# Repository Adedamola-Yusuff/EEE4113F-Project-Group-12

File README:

# EEE4113F_Group12_PCB
## Overview
This repository was used for Group 12 (of the 2026 EEE4113F course from the University of Cape Town) to collaborate on the design of the B.A.R.B.I.E.

Buoy for<br>
Antarctic<br>
Research and<br>
Basic<br>
Information<br>
Exchange

See the README within each directory for more information.

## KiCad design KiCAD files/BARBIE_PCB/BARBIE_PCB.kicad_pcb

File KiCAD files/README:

# EEE4113F_Group12_PCB - KiCAD files
## Overview
This PCB was intended to eventually be sent to [JLCPCB](https://jlcpcb.com/) for printing.

## What is included
This repository includes:
- The Project file
- The Schematic file
- The PCB file
Apologies for the files being so messy.

None of the generated gerber files are included.

## Installation & Dependencies
The files were made with KiCAD 9.0, so the same or a later version of KiCAD is needed to open the files.

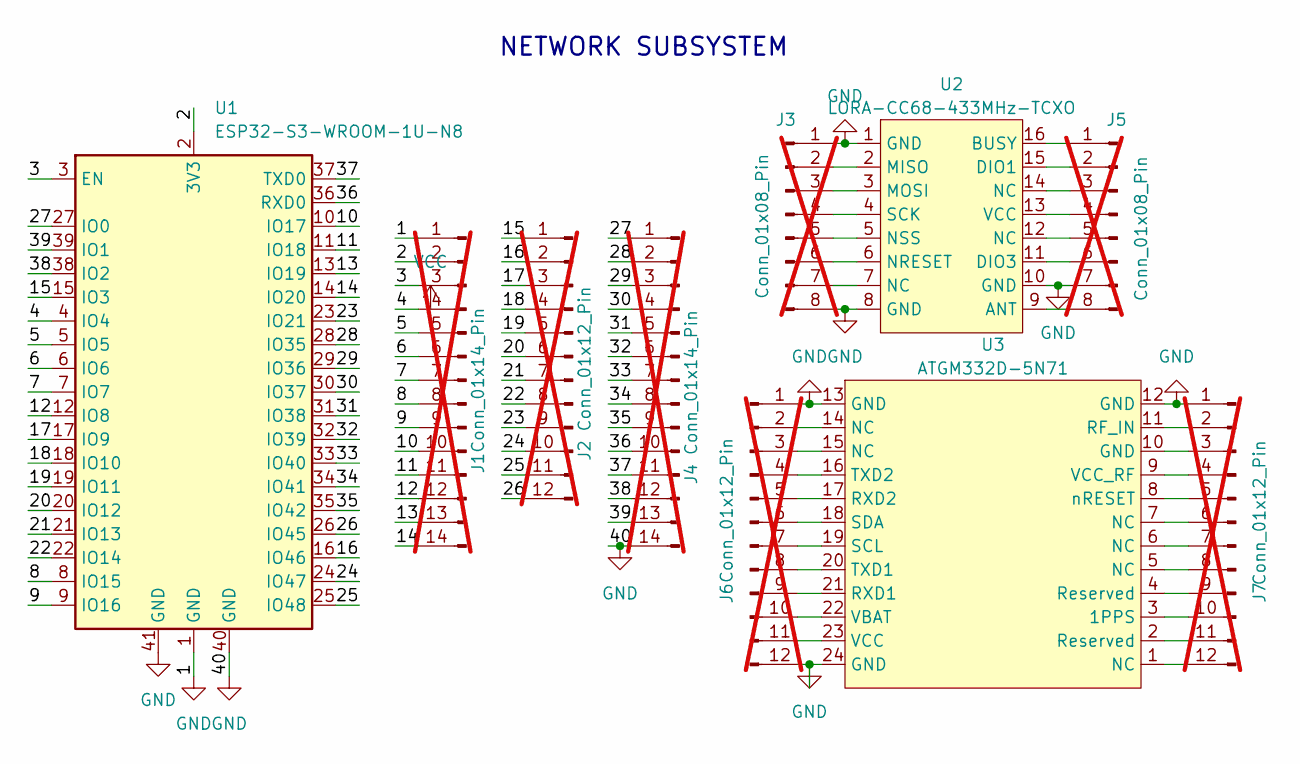
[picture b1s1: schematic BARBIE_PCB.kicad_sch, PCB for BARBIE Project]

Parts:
J1: Conn_01x14_Pin; PinHeader_1x14_P2.54mm_Vertical; not fitted
J2, J6, J7: Conn_01x12_Pin; PinHeader_1x12_P2.54mm_Vertical; not fitted
J3, J5: Conn_01x08_Pin; PinHeader_1x08_P2.54mm_Vertical; not fitted
J4: Conn_01x14_Pin; PinSocket_1x14_P2.54mm_Vertical; not fitted
U1: ESP32-S3-WROOM-1U-N8; ESP32-S3-WROOM-1U_No_holes; LCSC C2980297
U2: LORA-CC68-433MHz-TCXO; LCSC C5126744
U3: ATGM332D-5N71; ATGM332D-5NR32; LCSC C46955987

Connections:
/2: J1.2, U1.2 (3V3)
/3: J1.3, U1.3 (EN)
/4: J1.4, U1.4 (IO4)
/5: J1.5, U1.5 (IO5)
/6: J1.6, U1.6 (IO6)
/7: J1.7, U1.7 (IO7)
/8: J1.8, U1.8 (IO15)
/9: J1.9, U1.9 (IO16)
/10: J1.10, U1.10 (IO17)
/11: J1.11, U1.11 (IO18)
/12: J1.12, U1.12 (IO8)
/13: J1.13, U1.13 (IO19)
/14: J1.14, U1.14 (IO20)
/15: J2.1, U1.15 (IO3)
/16: J2.2, U1.16 (IO46)
/17: J2.3, U1.17 (IO9)
/18: J2.4, U1.18 (IO10)
/19: J2.5, U1.19 (IO11)
/20: J2.6, U1.20 (IO12)
/21: J2.7, U1.21 (IO13)
/22: J2.8, U1.22 (IO14)
/23: J2.9, U1.23 (IO21)
/24: J2.10, U1.24 (IO47)
/25: J2.11, U1.25 (IO48)
/26: J2.12, U1.26 (IO45)
/27: J4.1, U1.27 (IO0)
/28: J4.2, U1.28 (IO35)
/29: J4.3, U1.29 (IO36)
/30: J4.4, U1.30 (IO37)
/31: J4.5, U1.31 (IO38)
/32: J4.6, U1.32 (IO39)
/33: J4.7, U1.33 (IO40)
/34: J4.8, U1.34 (IO41)
/35: J4.9, U1.35 (IO42)
/36: J4.10, U1.36 (RXD0)
/37: J4.11, U1.37 (TXD0)
/38: J4.12, U1.38 (IO2)
/39: J4.13, U1.39 (IO1)
GND: J1.1, J3.1, J3.8, J4.14, J5.7, J6.1, J6.12, J7.1, U1.1 (GND), U1.40 (GND), U1.41 (GND), U2.1 (GND), U2.8 (GND), U2.10 (GND), U3.12 (GND), U3.13 (GND), U3.24 (GND)
unnamed: J3.2, U2.2 (MISO)
unnamed: J3.3, U2.3 (MOSI)
unnamed: J3.4, U2.4 (SCK)
unnamed: J3.5, U2.5 (NSS)
unnamed: J3.6, U2.6 (NRESET)
unnamed: J3.7, U2.7 (NC)
unnamed: J5.1, U2.16 (BUSY)
unnamed: J5.2, U2.15 (DIO1)
unnamed: J5.3, U2.14 (NC)
unnamed: J5.4, U2.13 (VCC)
unnamed: J5.5, U2.12 (NC)
unnamed: J5.6, U2.11 (DIO3)
unnamed: J5.8, U2.9 (ANT)
unnamed: J6.2, U3.14 (NC)
unnamed: J6.3, U3.15 (NC)
unnamed: J6.4, U3.16 (TXD2)
unnamed: J6.5, U3.17 (RXD2)
unnamed: J6.6, U3.18 (SDA)
unnamed: J6.7, U3.19 (SCL)
unnamed: J6.8, U3.20 (TXD1)
unnamed: J6.9, U3.21 (RXD1)
unnamed: J6.10, U3.22 (VBAT)
unnamed: J6.11, U3.23 (VCC)
unnamed: J7.2, U3.11 (RF_IN)
unnamed: J7.3, U3.10 (GND)
unnamed: J7.4, U3.9 (VCC_RF)
unnamed: J7.5, U3.8 (nRESET)
unnamed: J7.6, U3.7 (NC)
unnamed: J7.7, U3.6 (NC)
unnamed: J7.8, U3.5 (NC)
unnamed: J7.9, U3.4 (Reserved)
unnamed: J7.10, U3.3 (1PPS)
unnamed: J7.11, U3.2 (Reserved)
unnamed: J7.12, U3.1 (NC)

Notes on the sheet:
NETWORK SUBSYSTEM

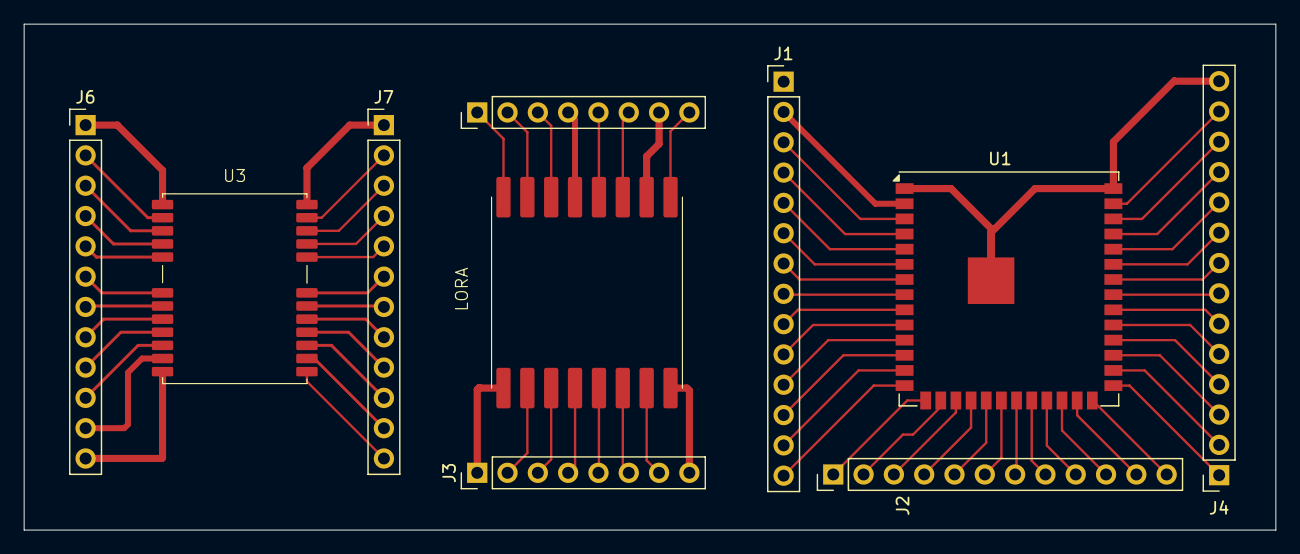
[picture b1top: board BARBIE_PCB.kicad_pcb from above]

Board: 2 copper layers, 104.9 x 42.4 mm, 10 parts (0 on the bottom side), 73 nets.

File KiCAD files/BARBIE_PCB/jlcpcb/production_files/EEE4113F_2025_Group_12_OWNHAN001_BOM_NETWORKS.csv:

Comment,Designator,Footprint,LCSC,Quantity
ESP32-S3-WROOM-1U-N8,U1,ESP32-S3-WROOM-1U_No_holes,C2980297,1
ATGM332D-5N71,U3,ATGM332D-5NR32,C46955987,1
LORA-CC68-433MHz-TCXO,U2,LORA-CC68-433MHz-TCXO,C5126744,1

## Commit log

2026-04-06 Added a voltage regulators and a switch. Still need to finish adding footprints.
2026-04-06 Starting PCB layout and tracing
2026-04-07 NETWORKS SUBSYSTEM
    Complete PCB design of my networks subsystem
2026-04-08 Integrated Hannah's schematic into the main schematic
2026-04-08 Integrated Hannah's PCB onto the main circuit. Now I have to do a force push.
2026-05-06 Created the development environment
2026-05-11 Pin configuration
2026-05-11 Extended gitignore and renamed folder
2026-05-15 LoRa and WiFi Communication Software
    Useful functions to communicate and operate the LoRa and WiFi modules. These functions were created so that they may easily be used by other subsystems.
2026-05-18 HTML & GPS
    HTML for UI as well as the GPS functions used
2026-05-18 Update README with project component descriptions
    Added descriptions for HTML, KiCAD, and embedded software sections.
2026-05-22 Cleaned up files and updated READMEs
2026-05-22 Added BARBIE User Manual
